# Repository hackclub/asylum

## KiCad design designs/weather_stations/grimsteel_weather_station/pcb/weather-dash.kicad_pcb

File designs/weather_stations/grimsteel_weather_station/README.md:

# grimsteel's weather station

## Features:
- Displays:
    - Weekly weather
    - Data from Home Assistant (soon)
- DHT11 sensor
- Two buttons
- Battery powering + charging
- Buzzer

## PCB
Here's a picture of my schematif! 

Schematic            |  PCB
:-------------------------:|:-------------------------:
  |  

*I'm using a WeMos ESP32-S2 module because of the added pins!*

[x] I ran DRC in KiCad and have made sure there are 0 errors!

## CAD Model:

The PCB is fastened using 3 M3 Heatset inserts and 3 M3 screws.
The case itself snaps together.

## Firmware overview

The firmware is written using ESP-IDF. It gets all data from Home Assistant

[x] I remembered to exclude any personal information, including API Keys, WiFi passwords, etc

## BOM
All prices must be in USD.

**Provided by dari // alex**:
- 1x WeMos S2 Mini WITHOUT FEMALE HEADERS
- 1x ST7735 1.8" LCD display WITHOUT FEMALE HEADERS. Male headers soldered!

**I will be sourcing the following parts with my grant**:
- 1x PCB from JLCPCB
    - $2 for 5x + $1.50 shipping
- 2x JST PH-2.0 connector + wires/plug [Aliexpress](https://www.aliexpress.us/item/3256806041370367.html) $1.08 (includes 5)
- 1x 3 pin SPDT switch - 0.5A [Aliexpress](https://www.aliexpress.us/item/2255800513009332.html) $0.84 (includes 10)
- 1x 1N5817 diode [Aliexpress](https://www.aliexpress.us/item/3256801365779334.html) $1.01 (includes 50)
- 1x TP4056 board [Aliexpress](https://www.aliexpress.us/item/3256804241424963.html) $1.29 (includes 5)
- 2x Tactile button cap - gray [Aliexpress](https://www.aliexpress.us/item/2251832842559353.html) $2.89 (includes 20)
- 3x M3/4.5mm, 3.5mm long Heatset Inserts  [Aliexpress](https://www.aliexpress.us/item/3256803396040989.html) $1.86 (includes 50)
- M3 heatset insert soldering iron tip [Aliexpress](https://www.aliexpress.us/item/3256806515637370.html) $2.37
- 1x 3pin Battery Spring compression contact (BC-35-3P) [Aliexpress](https://www.aliexpress.us/item/2255800016944760.html) $2.28 (includes 5)

**Total before tax**: $13.62 (all items are eligible for free shipping)

**I'll also be source the following parts myself since I already have them and would like to help Hack Club**:
- 1x 3D printed case
- 1x DHT11 board
- 2x 12mm push button
- 1x 10 ohm resistor
- 1x 1x3 female header (DHT11)
- 2x 2x8 male header (WeMos)
- 1x buzzer
- 1x Li-ion battery

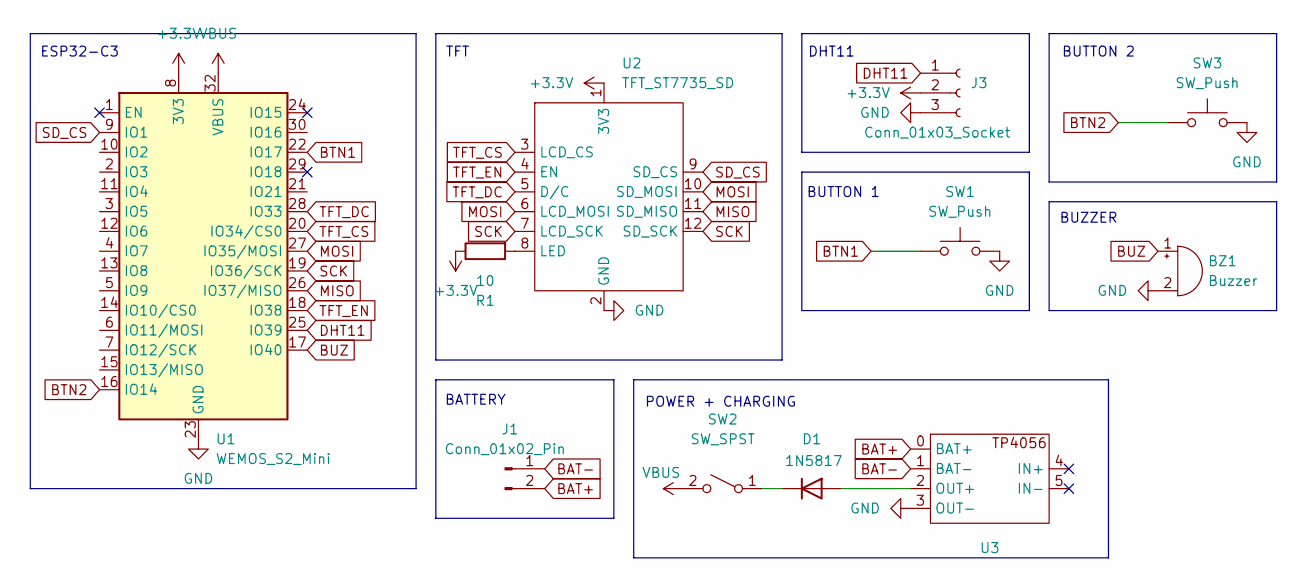
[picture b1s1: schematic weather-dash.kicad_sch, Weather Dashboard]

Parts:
BZ1: Buzzer; Buzzer_12x9.5RM7.6
D1: 1N5817; D_DO-41_SOD81_P7.62mm_Horizontal
J1: Conn_01x02_Pin; JST_PH_B2B-PH-K_1x02_P2.00mm_Vertical
J3: Conn_01x03_Socket; DHT11
R1: 10; R_Axial_DIN0207_L6.3mm_D2.5mm_P7.62mm_Horizontal
SW1, SW3: SW_Push; SW_PUSH_6mm_H4.3mm
SW2: SW_SPST; JST_PH_B2B-PH-K_1x02_P2.00mm_Vertical
U1: WEMOS_S2_Mini
U2: TFT_ST7735_SD
U3: TP4056

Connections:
+3.3V: J3.2, R1.1, U1.8 (3V3), U2.1 (3V3)
BAT+: J1.2, U3.0 (BAT+)
BAT-: J1.1, U3.1 (BAT-)
BTN1: SW1.1, U1.22 (IO17)
BTN2: SW3.1, U1.16 (IO14)
BUZ: BZ1.1 (+), U1.17 (IO40)
DHT11: J3.1, U1.25 (IO39)
GND: BZ1.2 (-), J3.3, SW1.2, SW3.2, U1.23 (GND), U2.2 (GND), U3.3 (OUT-)
MISO: U1.26 (IO37/MISO), U2.11 (SD_MISO)
MOSI: U1.27 (IO35/MOSI), U2.6 (LCD_MOSI), U2.10 (SD_MOSI)
unnamed: D1.2 (A), U3.2 (OUT+)
unnamed: D1.1 (K), SW2.1 (A)
unnamed: R1.2, U2.8 (LED)
SCK: U1.19 (IO36/SCK), U2.7 (LCD_SCK), U2.12 (SD_SCK)
SD_CS: U1.9 (IO1), U2.9 (SD_CS)
TFT_CS: U1.20 (IO34/CS0), U2.3 (LCD_CS)
TFT_DC: U1.28 (IO33), U2.5 (D/C)
TFT_EN: U1.18 (IO38), U2.4 (EN)
VBUS: SW2.2 (B), U1.32 (VBUS)

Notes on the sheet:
BUTTON 2
BUTTON 1
ESP32-C3
POWER + CHARGING
TFT
DHT11
BUZZER
BATTERY

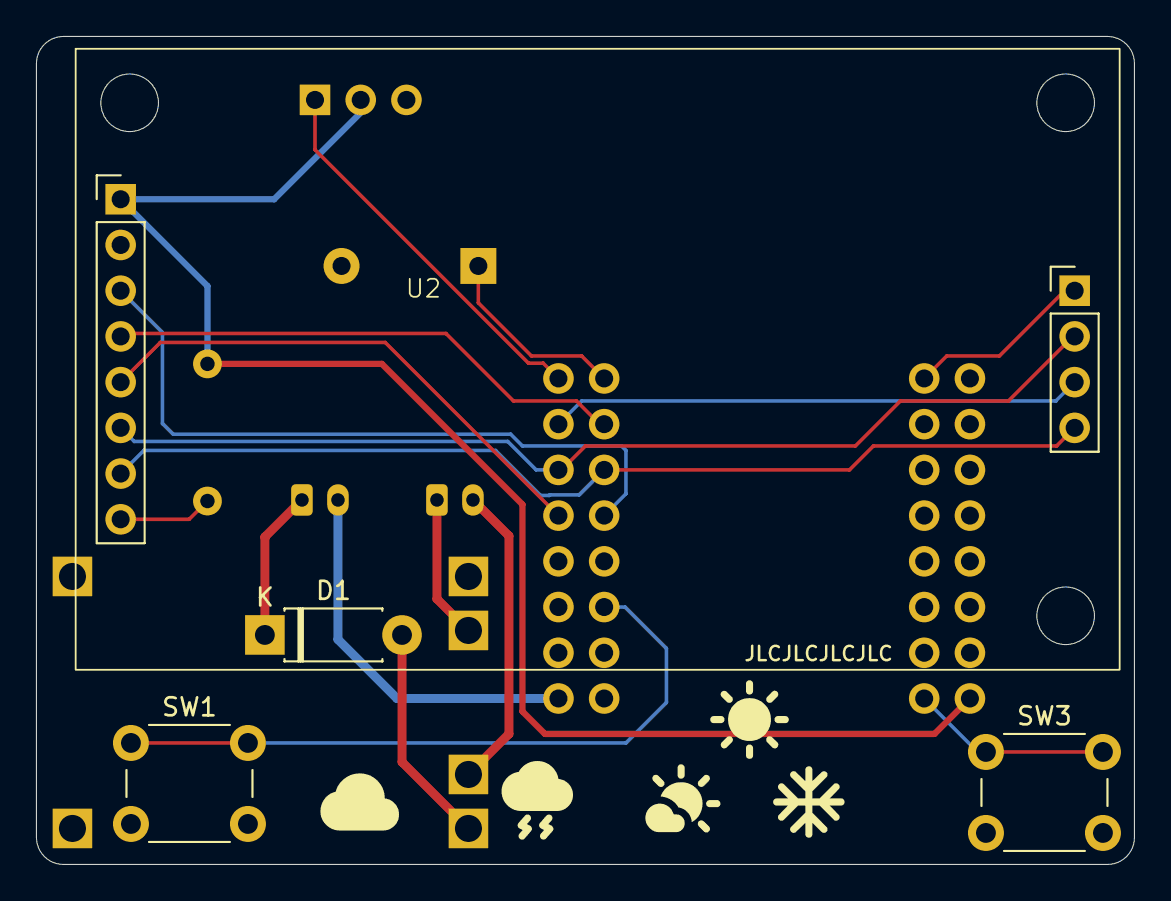
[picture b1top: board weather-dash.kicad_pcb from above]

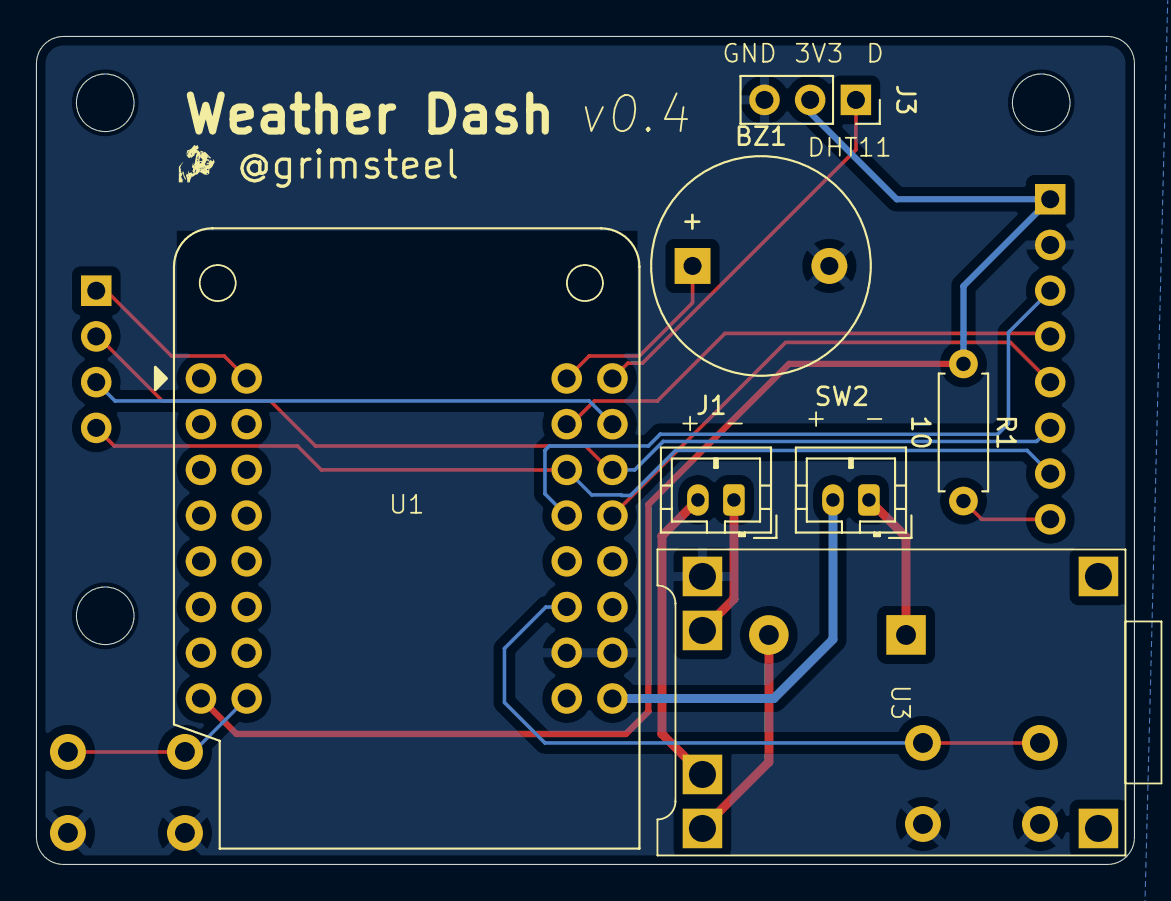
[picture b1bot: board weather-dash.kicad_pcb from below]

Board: 11 copper layers, 61.0 x 46.0 mm, 11 parts (7 on the bottom side), 19 nets.

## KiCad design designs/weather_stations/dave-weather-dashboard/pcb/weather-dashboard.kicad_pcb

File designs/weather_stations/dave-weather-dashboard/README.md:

# Dave's Weather Dashboard

This is a weather dashboard I made.

## Features

- Fetching from BMKG's API
- Displays: Weather information

## Firmware Overview

The firmware is located in the [firmware folder](./firmware) made using [PlatformIO](https://platformio.org/). To open using PlatformIO, open the [firmware](./firmware).

## CAD Model

The design was made using [Autodesk Fusion](https://www.autodesk.com/education/edu-software/fusion) is located in the [cad folder](./cad).

## PCB

The PCB was made using [KiCad](https://www.kicad.org/) 8.99 located in the [pcb folder](./pcb).

Schematic | PCB
:-:|:-:
 | 

## BOM

All prices must be in USD.

**Provided by dari // alex**:
- 1x WeMos S2 Mini WITHOUT FEMALE HEADERS
- 1x ST7735 1.8" LCD display WITHOUT FEMALE HEADERS. Male headers soldered!

**I will be sourcing the following parts with my grant**:

- 1x PCB from JLCPCB
    - $4 for 5x + $1.50 for shipping
- 2x 10 uF 1206 3216(mm) SMD Capacitor [Tokopedia](https://www.tokopedia.com/cosmic-iot/capacitor-10uf-10-uf-0603-kapasitor-microfarad-smd) $0.13
- 1x 18650 Li-ion Battery [Tokopedia](https://www.tokopedia.com/alladinshop/original-baterai-lion-18650-high-drain-real-capacity-2500mah-3-7v-3-7volt-li-ion) $0.76
- 1x Resistor SMD 1206 3216(mm) 50k Ohm [Tokopedia](https://www.tokopedia.com/smgjayatronik/resistor-smd-1206-50-kiloohm-50k-50-k) $0.13 (includes 10)
- 1x Resistor SMD 1206 3216 (mm) 10 Ohm [Tokopedia](https://www.tokopedia.com/smgjayatronik/resistor-smd-1206-10-ohm) $0.08 (includes 10)
- 1x Resistor SMD 1206 3216 (mm) 1k Ohm [Tokopedia](https://www.tokopedia.com/smgjayatronik/resistor-smd-1206-1-6k-1k6-ohm) $0.08 (includes 10)
- 1x Resistor SMD 1206 3216 (mm) 100k Ohm [Tokopedia](https://www.tokopedia.com/smgjayatronik/resistor-smd-1206-100-kiloohm-100k-100-k) $0.08 (includes 10)
- 1x O3401A SOT-23 MOSFET [Tokopedia](https://www.tokopedia.com/lisuinstrument/ao3401-3401-a19t-30v-p-channel-mosfet-ao3401a-sot-23-generic-biasa-3b2c) $0.02
- 1x LED SMD 1206 [Tokopedia](https://www.tokopedia.com/jogjarobotika/led-smd-1206-hijau) $0.02
- 1x 18650 Battery Holder [Tokopedia](https://www.tokopedia.com/mikro-automasi/dudukan-baterai-batre-18650-battery-holder-1-satu-slot) $0.13

Tokopedia before shipping: $1.37
Tokopedia after shipping: $4.14 (estimation)
Total: $8.64 (estimation)

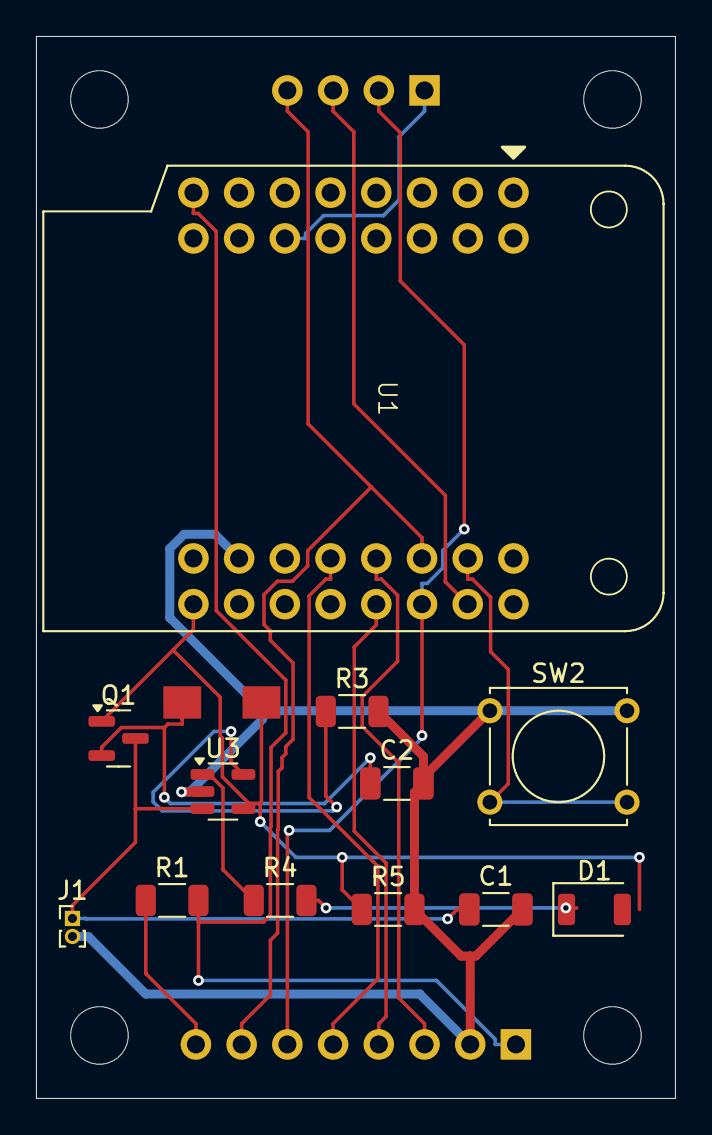
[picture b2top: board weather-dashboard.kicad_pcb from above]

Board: 2 copper layers, 35.5 x 59.0 mm, 14 parts (1 on the bottom side), 17 nets.

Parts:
C1: C1; C_1206_3216Metric
C2: C2; C_1206_3216Metric
D1: ORANGE; LED_1206_3216Metric_ReverseMount_Hole1.8x2.4mm
D2: D_Schottky; DO-214AC
J1: Conn_01x02_MountingPin; PinHeader_1x02_P1.00mm_Vertical
Q1: SL2301S; SOT-23
R1: R1; R_1206_3216Metric
R3: 50k; R_1206_3216Metric
R4: 1k; R_1206_3216Metric
R5: 100k; R_1206_3216Metric
SW2: SW_Omron_B3FS; SW_Tactile_Straight_KSA0Axx1LFTR
U1: WEMOS_S2_Mini
U3: MCP73831-2-OT; SOT-23-5
U4: U4; TFT_ST7735_SD

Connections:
+3V3: R1.2, U1.8 (3V3), U4.1 (3V3)
+BATT: C1.1, J1.1, Q1.3 (D), U3.3 (V_{BAT})
Button: SW2.2, U1.18 (IO38)
GND: C1.2, C2.2, J1.2, R3.2, R5.2, SW2.1, U1.23 (GND), U3.2 (V_{SS}), U4.2 (GND)
MISO: U1.26 (IO37/MISO), U4.11 (SD_MISO)
MOSI: U1.27 (IO35/MOSI), U4.6 (LCD_MOSI), U4.10 (SD_MOSI)
unnamed: D1.1 (K), R4.2
unnamed: R3.1, U3.5 (PROG)
unnamed: R4.1, U3.1 (STAT)
unnamed: R1.1, U4.8 (LED)
SCK: U1.19 (IO36/SCK), U4.7 (LCD_SCK), U4.12 (SD_SCK)
SD_CS: U1.14 (IO10/CS0), U4.9 (SD_CS)
TFT_CS: U1.20 (IO34/CS0), U4.3 (LCD_CS)
TFT_DC: U1.21 (IO21), U4.5 (D/C)
TFT_EN: U1.28 (IO33), U4.4 (EN)
VBUS: D1.2 (A), D2.2 (A), Q1.1 (G), R5.1, U1.32 (VBUS), U3.4 (V_{DD})
VCC: C2.1, D2.1 (K), Q1.2 (S)

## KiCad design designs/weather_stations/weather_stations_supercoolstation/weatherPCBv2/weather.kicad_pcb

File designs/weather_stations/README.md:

# weather station
Here's my submission for my weather station! Under the asylum "dragons_weather"

## Features:
- Displays:
    - Date
    - Temperature 
    - Settings
- 4 WS2812Bs for dynamic LED effects
- A switch for turning on and off
- Slider for settings

## PCB
Here's a picture of my schematic, I wired a Wemos ESP32-S3 module to a TFT display, 5 WS2812B LEDs, a slider for settings

Schematic            |  PCB
:-------------------------:|:-------------------------:

tic.png)  |  

[ x ] I ran DRC in KiCad and have made sure there are 0 errors!

## CAD Model:
Everything fits together using 4 M3 Heatset inserts

## Firmware overview
Firmware is written in aurdino, it grabs data from a API. Code for turining it off and on, slider and basic settings are written

[ x ] I remembered to exclude any personal information, including API Keys, WiFi passwords, etc

#BOM
**Provided by dari // alex**:
- 1x WeMos S2 Mini WITHOUT FEMALE HEADERS
- 1x ST7735 1.8" LCD display WITHOUT FEMALE HEADERS. Male headers soldered!

I will buy 4 WS2812Bs, which will cost me $0.8 in total.
I will be sourcing the following parts with my grant:
- 1x PCB from JLCPCB
    - $2 for 5x + $1.50 shipping

- 1x SPDT slide switch [(ADAFRUIT)](https://www.adafruit.com/product/4219) $2.95

Total before tax: $6.5

I'll also be source the following parts myself since I already have them and would like to help Hack Club:

- 3d PRINT

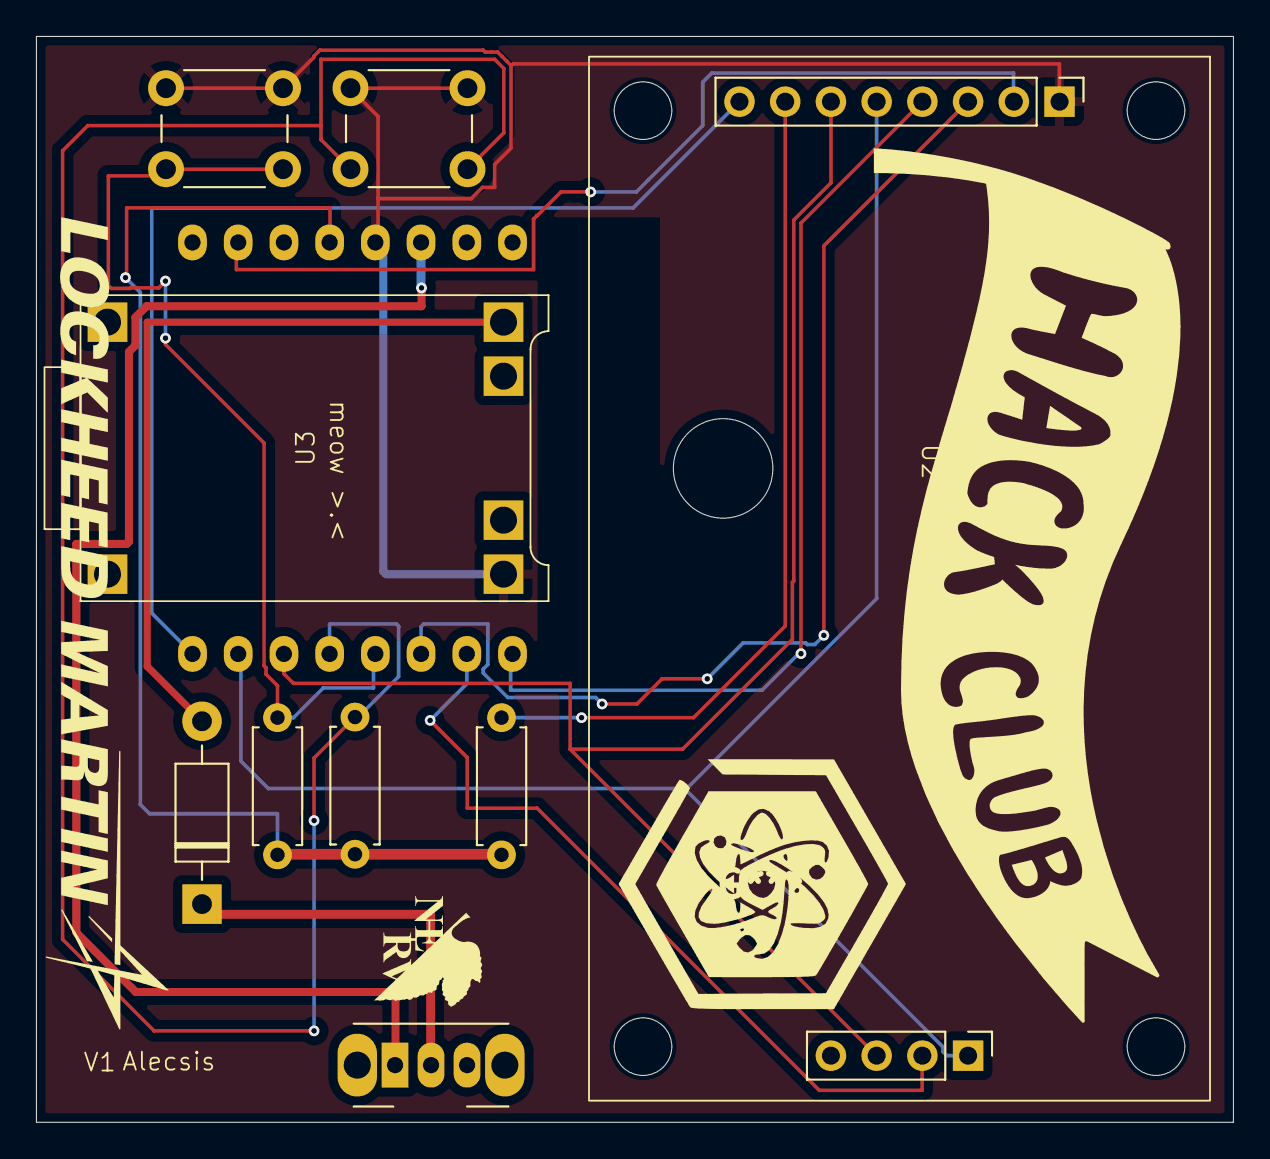
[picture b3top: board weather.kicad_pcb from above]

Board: 2 copper layers, 66.5 x 60.3 mm, 10 parts (1 on the bottom side), 15 nets.

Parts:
D1: 1N5817; D_DO-41_SOD81_P10.16mm_Horizontal
R2: 10; R_Axial_DIN0207_L6.3mm_D2.5mm_P7.62mm_Horizontal
R5, R6: 10K; R_Axial_DIN0207_L6.3mm_D2.5mm_P7.62mm_Horizontal
SW1, SW2: SW_Push; SW_PUSH_6mm_H9.5mm
SW3: SW_SPDT; SW_Slide_SPDT_Angled_CK_OS102011MA1Q
U1: WEMOS_C3_mini
U2: TFT_ST7735_SD
U3: TP4056

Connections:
+3.3V: R2.2, R5.1, R6.1, U1.12 (3.3V)
AO: U1.1 (A1), U2.4 (AO)
B1: R5.2, SW1.1, U1.4 (A4)
B2: R6.2, SW2.1, U1.5 (A5)
Batt_Out: D1.2 (A), U3.2 (OUT+)
CS: U1.10, U2.2 (~CS)
GND: SW1.2, SW2.2, U1.13 (GND), U2.1 (GND), U3.3 (OUT-)
MISO: U1.2 (A2), U2.10 (SD_MISO)
MOSI: U1.7 (7/RGB_LED), U2.5 (SDA), U2.9 (SD_MOSI)
unnamed: D1.1 (K), SW3.2 (B)
unnamed: R2.1, U2.7 (LED)
RESET: U1.3 (A3), U2.3 (RESET)
SCK: U1.6, U2.6 (SCK), U2.11 (SD_SCK)
SD_CS: U1.8, U2.8 (SD_CS)
VCC: SW3.1 (A), U1.14 (VBUS)

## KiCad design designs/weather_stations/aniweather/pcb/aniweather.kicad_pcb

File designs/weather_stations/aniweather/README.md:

<h1 align="center">Aniweather - Your personal anime weather station!</h1>

This is a 3D weather station! You can choose between displaying daily waifu pics and the current weather. **No external libraries used!**

Made for #asylum. The main API code is at https://github.com/cheyao/short with nest :D

To change the settings, edit `firmware/settings.h`! The weather info is mostly parsed on nest.

[ x ] I ran DRC in KiCad and have made sure there are 0 errors!

### BOM 
Provided by dari // alex:
- 1x WeMos S2 Mini (as a cheaper replacement for the S2) WITHOUT FEMALE HEADERS
- 1x ST7735 1.8" LCD display WITHOUT FEMALE HEADERS. Male headers soldered!

Purchasing from HQ:
- 2x 1N4148 at ???$

I will be sourcing the following parts with my grant:
- 1x PCB from JLCPCB
    - $2 for 5x + $1.50 shipping
- 2x 2-1825910-7             0,17 $ - 0,51 $
- 1x NR3015T2R2M             0,31 $ - 0,31 $ 
- 4x FG16X7R1E106KRT06       0,84 $ - 3,36 $
- 1x TPS63001DRCR            2,16 $ - 2,16 $
- 1x 3D printed case         self print

Total: 8.34 $ + Lipo from aliexpress

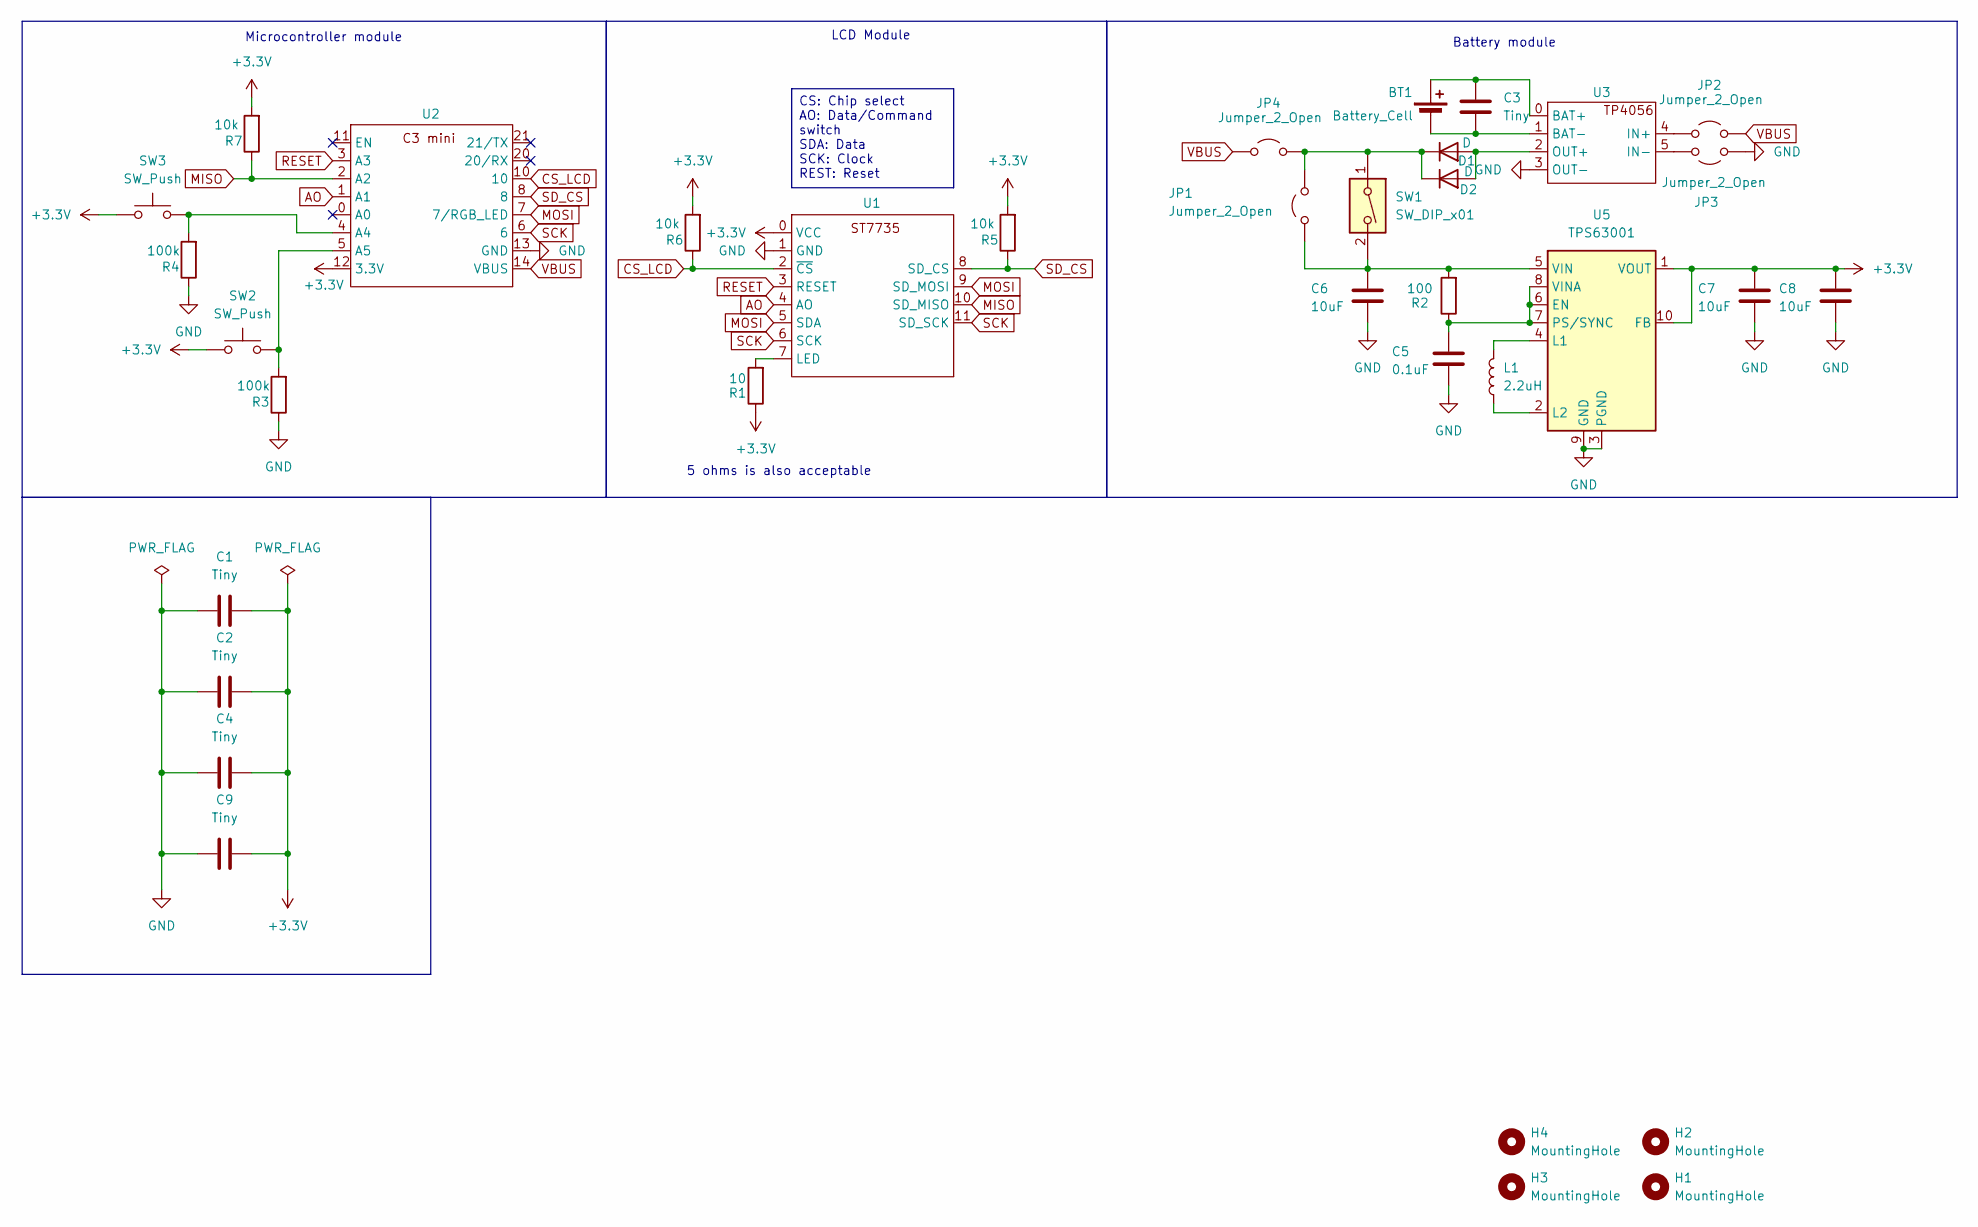
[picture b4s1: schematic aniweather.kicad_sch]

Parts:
BT1: Battery_Cell; TestPoint_2Pads_Pitch5.08mm_Drill1.3mm
C1, C2, C3, C4, C9: Tiny; C_Disc_D5.0mm_W2.5mm_P2.50mm
C5: 0.1uF; C_Disc_D5.0mm_W2.5mm_P2.50mm
C6, C7, C8: 10uF; C_Disc_D5.0mm_W2.5mm_P2.50mm
D1, D2: D; D_DO-35_SOD27_P7.62mm_Horizontal
H1, H2, H3, H4: MountingHole; MountingHole_3.2mm_M3
JP1, JP2, JP3, JP4: Jumper_2_Open; SolderJumper-2_P1.3mm_Open_Pad1.0x1.5mm
L1: 2.2uH; NR3015T2R2M
R1: 10; R_Axial_DIN0207_L6.3mm_D2.5mm_P10.16mm_Horizontal
R2: 100; R_Axial_DIN0207_L6.3mm_D2.5mm_P10.16mm_Horizontal
R3, R4: 100k; R_Axial_DIN0207_L6.3mm_D2.5mm_P10.16mm_Horizontal
R5, R6, R7: 10k; R_Axial_DIN0207_L6.3mm_D2.5mm_P10.16mm_Horizontal
SW1: SW_DIP_x01; SW_DIP_SPSTx01_Slide_9.78x4.72mm_W7.62mm_P2.54mm
SW2, SW3: SW_Push; SW_PUSH_6mm
U1: ST7735
U2: WEMOS_C1_mini
U3: TP4056
U5: TPS63001; Texas_DRC0010J_ThermalVias

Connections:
+3.3V: C1.2, C2.2, C4.1, C7.1, C8.1, C9.1, R1.1, R5.2, R6.2, R7.2, SW2.1, SW3.1, U1.0 (VCC), U2.12 (3.3V), U5.1 (VOUT), U5.10 (FB)
AO: U1.4 (AO), U2.1 (A1)
CS_LCD: R6.1, U1.2 (~CS), U2.10
GND: C1.1, C2.1, C4.2, C5.2, C6.2, C7.2, C8.2, C9.2, JP3.1 (A), R3.1, R4.1, U1.1 (GND), U2.13 (GND), U3.3 (OUT-), U5.3 (PGND), U5.9 (GND), U5.11 (PGND)
MISO: R7.1, U1.10 (SD_MISO), U2.2 (A2)
MOSI: U1.5 (SDA), U1.9 (SD_MOSI), U2.7 (7/RGB_LED)
unnamed: BT1.1 (+), C3.1, U3.0 (BAT+)
unnamed: BT1.2 (-), C3.2, U3.1 (BAT-)
unnamed: D1.2 (A), D2.2 (A), U3.2 (OUT+)
unnamed: D1.1 (K), D2.1 (K), JP1.2 (B), JP4.2 (B), SW1.1
unnamed: C6.1, JP1.1 (A), R2.2, SW1.2, U5.5 (VIN)
unnamed: JP2.1 (A), U3.4 (IN+)
unnamed: JP3.2 (B), U3.5 (IN-)
unnamed: R1.2, U1.7 (LED)
unnamed: R4.2, SW3.2, U2.4 (A4)
unnamed: R3.2, SW2.2, U2.5 (A5)
unnamed: C5.1, R2.1, U5.6 (EN), U5.7 (PS/SYNC), U5.8 (VINA)
unnamed: L1.2, U5.4 (L1)
unnamed: L1.1, U5.2 (L2)
RESET: U1.3 (RESET), U2.3 (A3)
SCK: U1.6 (SCK), U1.11 (SD_SCK), U2.6
SD_CS: R5.1, U1.8 (SD_CS), U2.8
VBUS: JP2.2 (B), JP4.1 (A), U2.14 (VBUS)

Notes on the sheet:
Microcontroller module
Battery module
5 ohms is also acceptable
LCD Module
CS: Chip select AO: Data/Command switch SDA: Data SCK: Clock REST: Reset

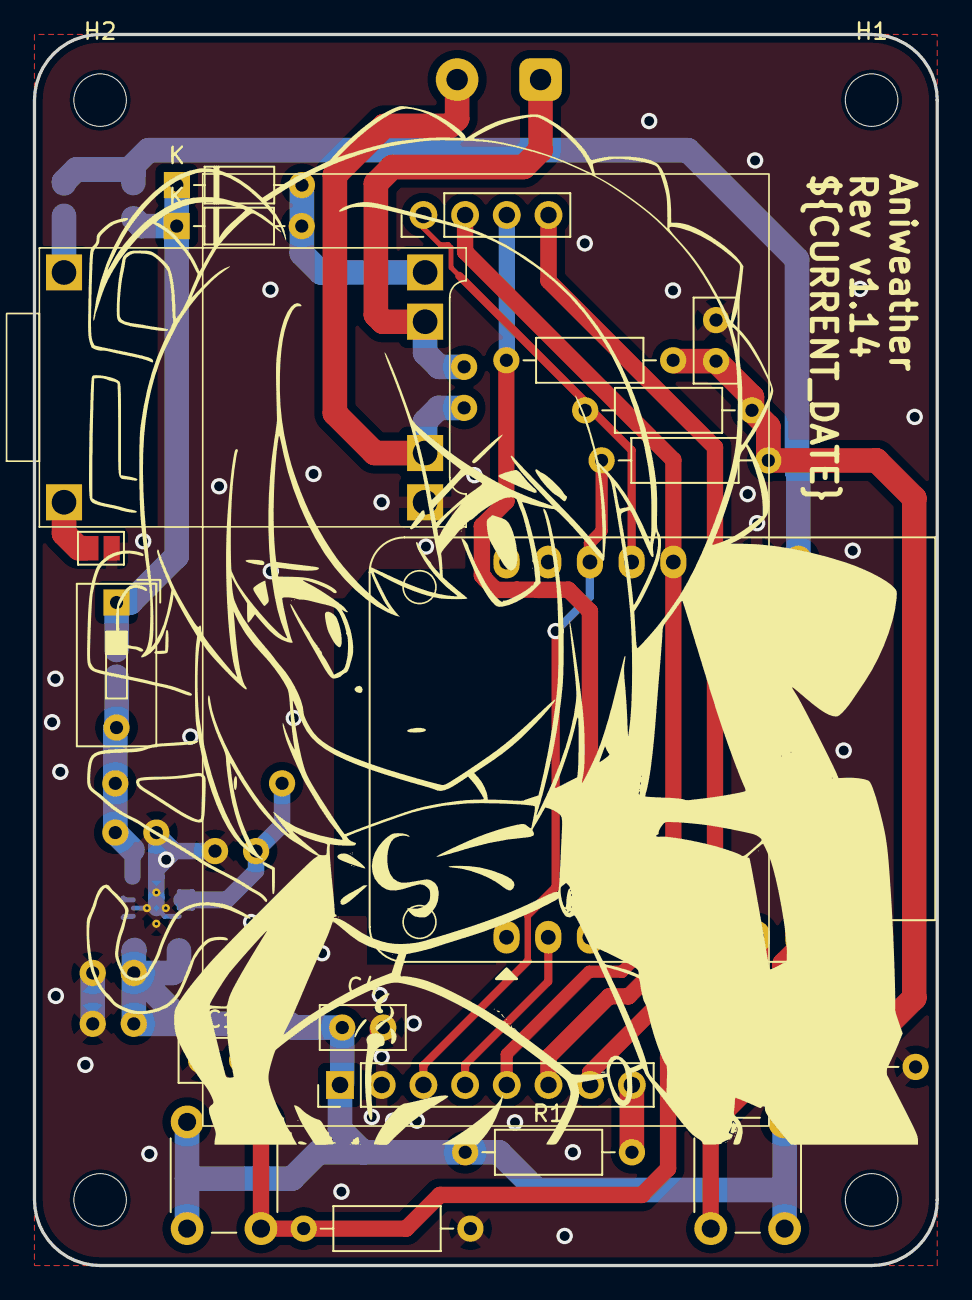
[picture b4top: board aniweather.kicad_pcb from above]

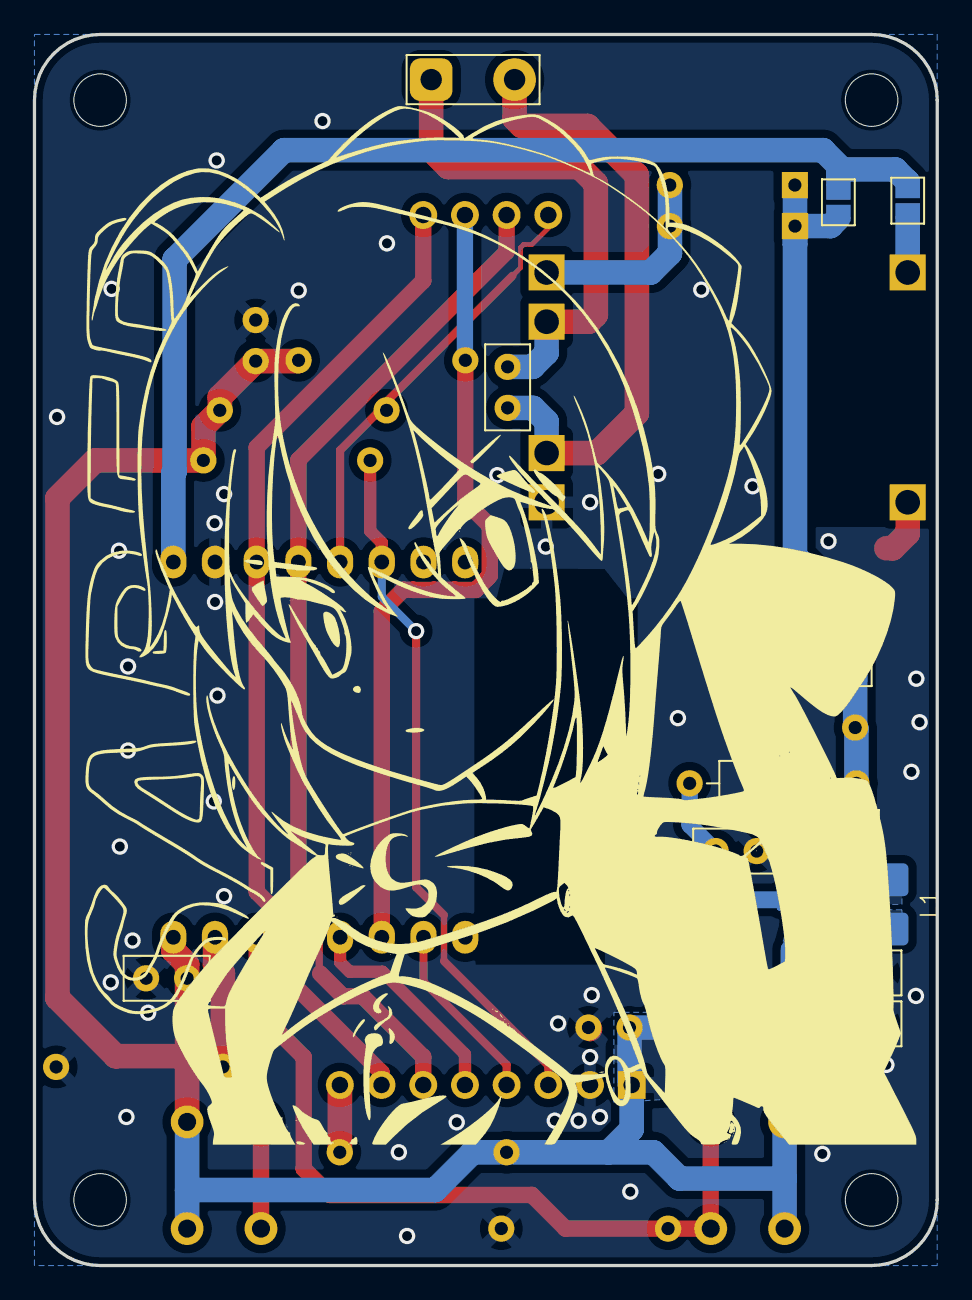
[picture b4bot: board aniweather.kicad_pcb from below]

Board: 2 copper layers, 55.0 x 75.0 mm, 37 parts (14 on the bottom side), 23 nets.

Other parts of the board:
G1, G2: LOGO

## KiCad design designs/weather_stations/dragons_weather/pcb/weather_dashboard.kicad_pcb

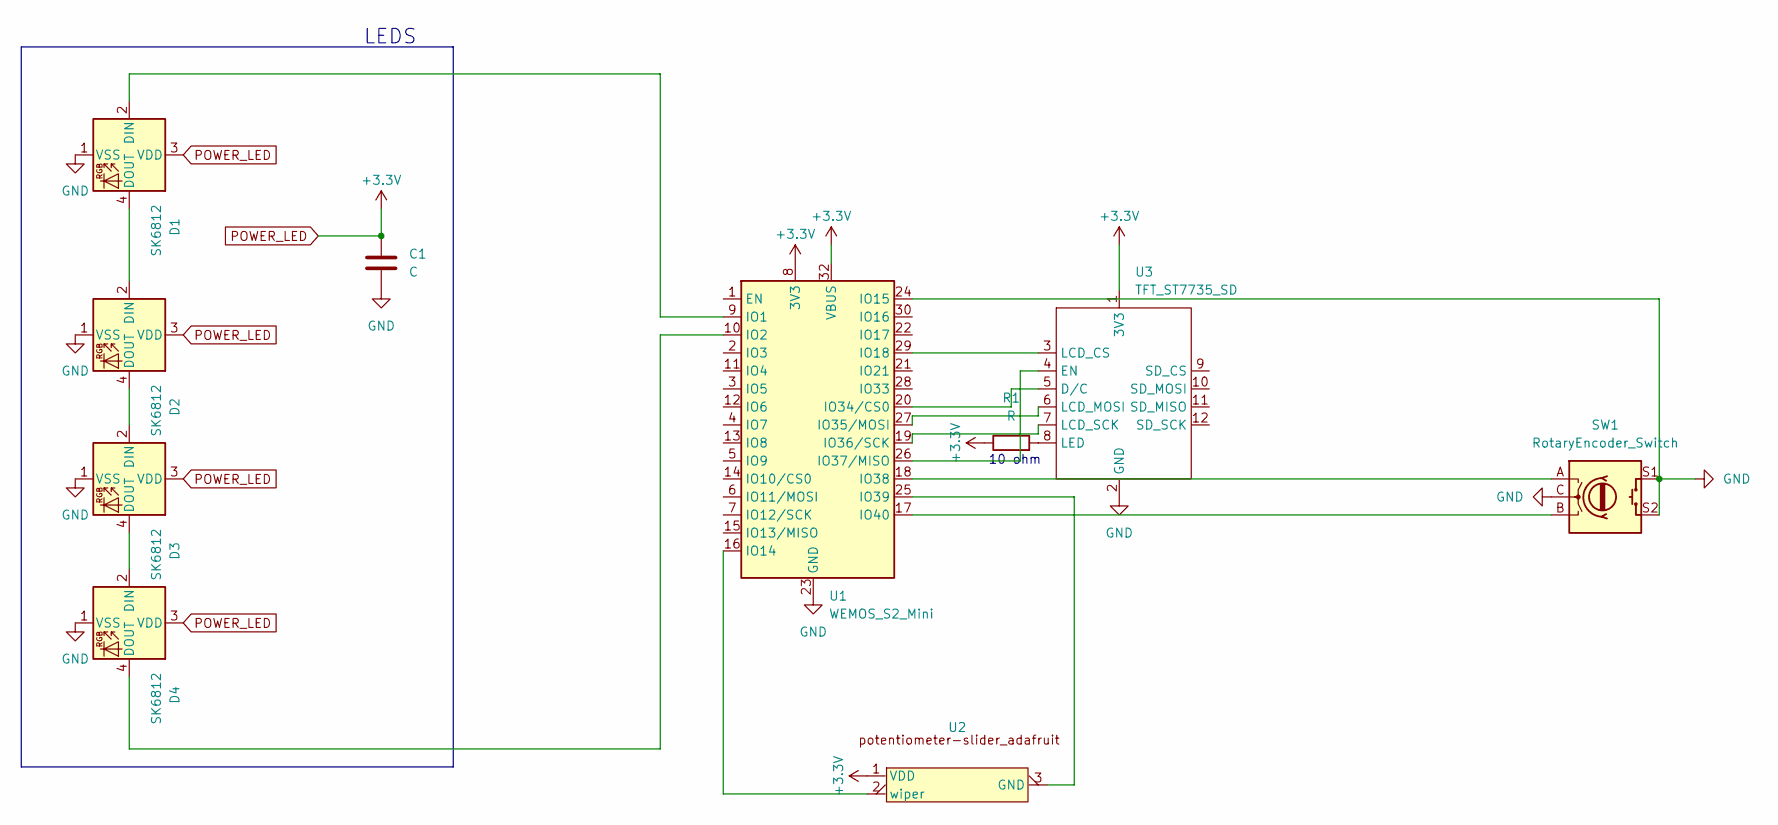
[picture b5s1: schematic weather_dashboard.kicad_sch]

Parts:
C1: C; CP_Axial_L10.0mm_D4.5mm_P15.00mm_Horizontal
D1, D2, D3, D4: SK6812; LED_SK6812_PLCC4_5.0x5.0mm_P3.2mm
R1: R; R_Array_SIP4
SW1: RotaryEncoder_Switch; RotaryEncoder_Alps_EC11E-Switch_Vertical_H20mm
U1: WEMOS_S2_Mini
U2: Potienometer-slider_adafruit
U3: TFT_ST7735_SD

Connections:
GND: C1.2, D1.1 (VSS), D2.1 (VSS), D3.1 (VSS), D4.1 (VSS), SW1.C, SW1.S1, SW1.S2, U1.23 (GND), U1.24 (IO15), U3.2 (GND)
unnamed: D1.2 (DIN), U1.9 (IO1)
unnamed: D1.4 (DOUT), D2.2 (DIN)
unnamed: D2.4 (DOUT), D3.2 (DIN)
unnamed: D3.4 (DOUT), D4.2 (DIN)
unnamed: D4.4 (DOUT), U1.10 (IO2)
unnamed: U1.16 (IO14), U2.2 (wiper)
unnamed: U1.29 (IO18), U3.3 (LCD_CS)
unnamed: U1.20 (IO34/CS0), U3.5 (D/C)
unnamed: U1.27 (IO35/MOSI), U3.6 (LCD_MOSI)
unnamed: U1.19 (IO36/SCK), U3.7 (LCD_SCK)
unnamed: U1.26 (IO37/MISO), U3.4 (EN)
unnamed: SW1.A, U1.18 (IO38)
unnamed: U1.25 (IO39), U2.3 (GND)
unnamed: SW1.B, U1.17 (IO40)
unnamed: R1.2, U3.8 (LED)
POWER_LED: C1.1, D1.3 (VDD), D2.3 (VDD), D3.3 (VDD), D4.3 (VDD), R1.1, U1.8 (3V3), U1.32 (VBUS), U2.1 (VDD), U3.1 (3V3)

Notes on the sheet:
LEDS
10 ohm

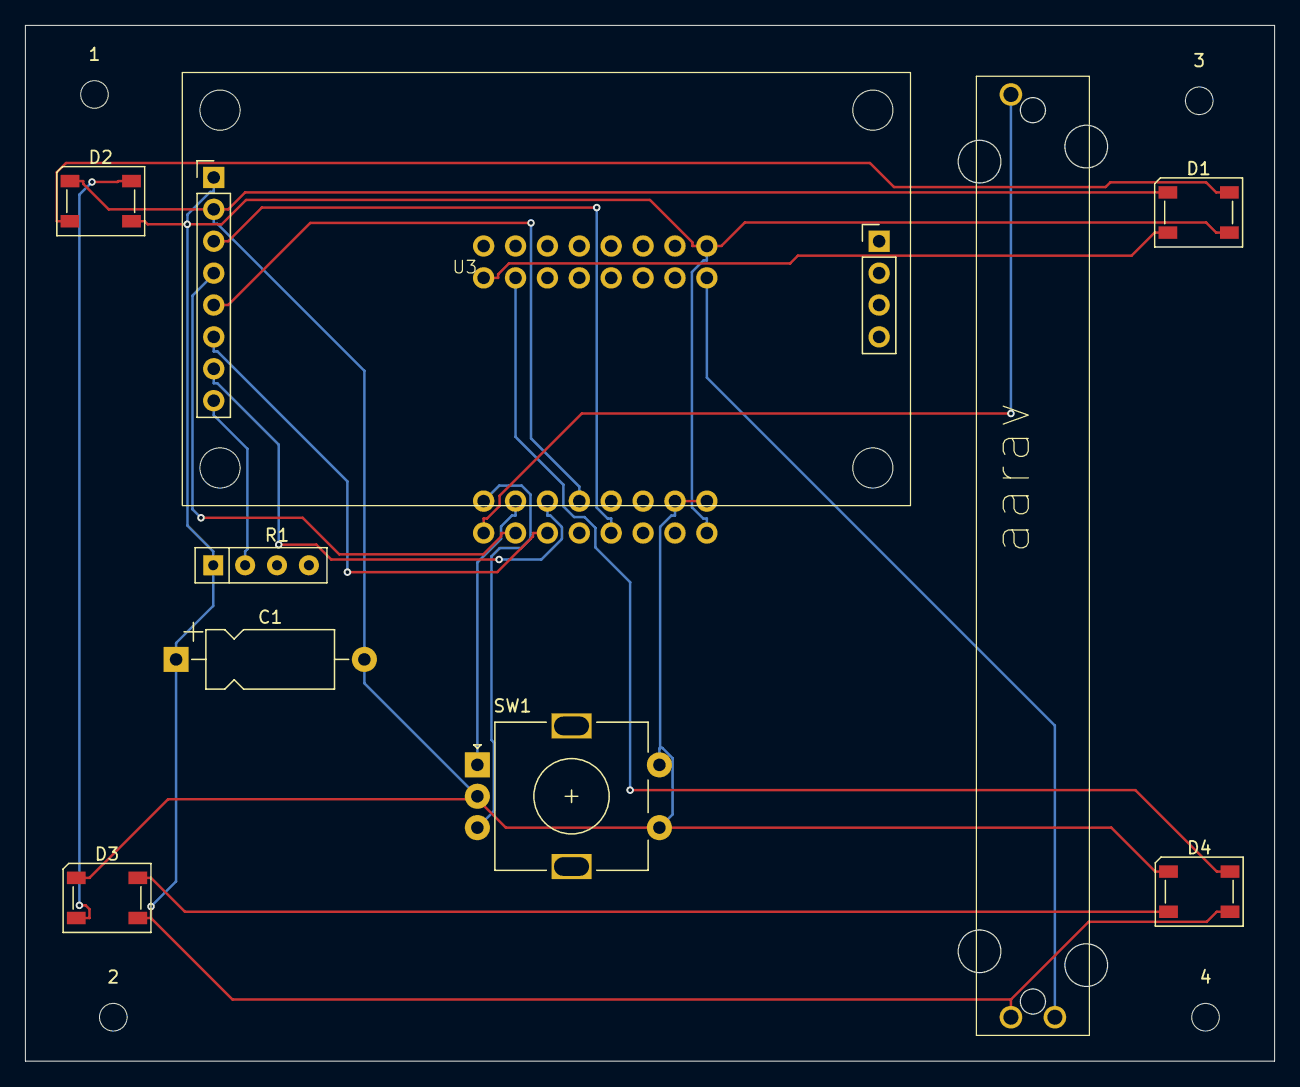
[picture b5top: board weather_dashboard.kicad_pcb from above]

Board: 2 copper layers, 99.5 x 82.5 mm, 14 parts (1 on the bottom side), 17 nets.

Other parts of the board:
1, 2, 3, 4: MountingHole_2.2mm_M2

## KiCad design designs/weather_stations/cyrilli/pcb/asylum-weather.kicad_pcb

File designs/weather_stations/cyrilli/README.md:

# cyrilli's weather station submission

<div align="center">
    
    &nbsp;
    &nbsp;
    
</div>

## BOM

- 1x Wemos/Lolin ESP32-C3 board
- 1x 1.8 inch TFT display
- 2x ELM3052 Triac
    - C142300
- 1x 75 Ohm 0603 Resistor
    - C4275
- 1x 10 Ohm 1206 Resistor
    - C17903
- 3x 2x8P 2.54mm Female Header
    - C5160823
- 8x M3 25mm Double-ended Standoff
- 2x M3 16mm Double-ended Standoff
- 4x M3 50mm Screw
- 2x M3 16mm Screw

## Planned Use

I plan to use this as a small display for agenda items or connect it to my computer to use as a status panel. I will also run wires to our garage door to act as a smart door opener.

## Design Process

The design was inspired by 龙少's stacked homebrew CPU design. Since the minimum order for PCBs is 5, I used the extra boards to sandwich the main board, acting as a case without needing extra 3D printed components. The PCB is perfectly square so that two layers can be rotated and stacked for the bottome case, covering all the drill holes and cutouts of each other. Pin connections between the LCD and the ESP32 was chosen to permit visually pleasing routing on a single layer.

## Case

I am planning to stack some unpopulated PCBs vertically for a homebrew-cpu-like "case" instead of using 3D printed parts.

## Firmware

Written in CircuitPython, will be expanded once I have hardware to test on.

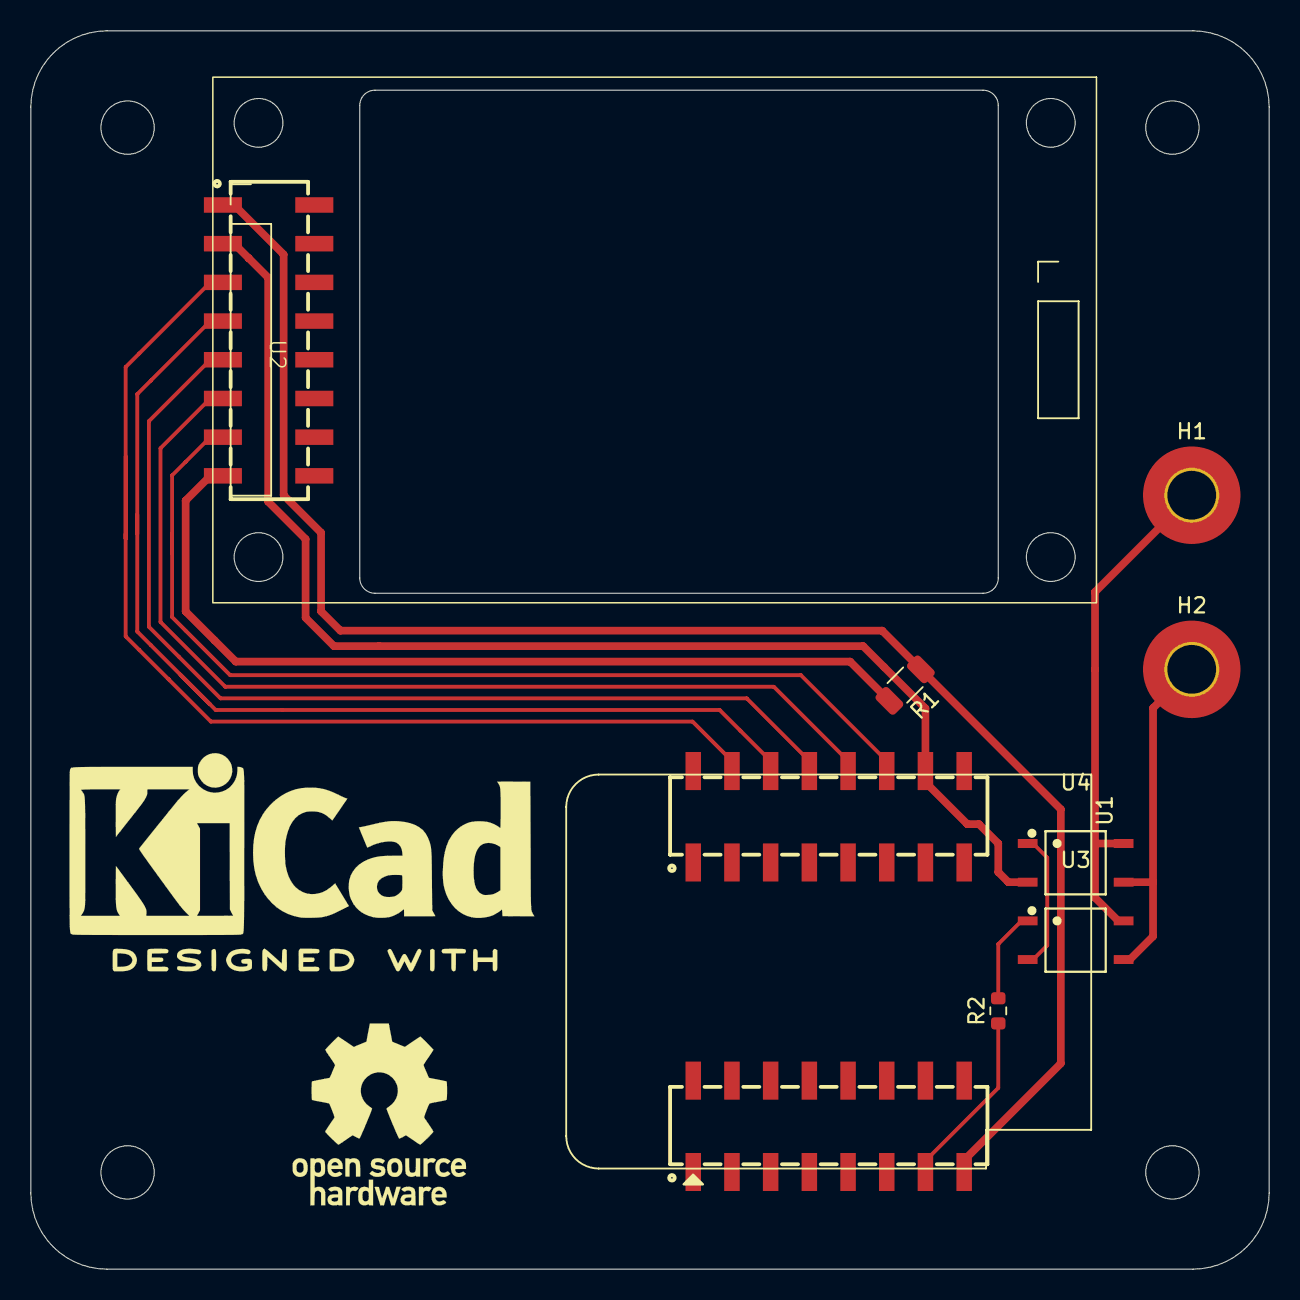
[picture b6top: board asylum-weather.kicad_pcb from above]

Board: 2 copper layers, 81.3 x 81.3 mm, 10 parts (0 on the bottom side), 13 nets.

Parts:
H1, H2: MountingHole_Pad; MountingHole_3.2mm_M3_Pad_TopBottom
J1, J2: Conn_02x08_Counter_Clockwise; HDR-SMD_16P-P2.54-V-F-R2-C8-LS7.1
R1: 10; R_1206_3216Metric
R2: 75; R_0603_1608Metric
U1: WEMOS_C3_Mini; WEMOS_C3_1
U2: TFT_ST7735_SD
U3, U4: ELM3052(TA); SOP-4_L4.4-W4.0-P2.54-LS7.0-TL

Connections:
unnamed: H1.1, U3.4 (Terminal), U4.4 (Terminal)
unnamed: H2.1, U3.3 (Terminal), U4.3 (Terminal)
unnamed: R1.2, U2.8 (LED)
unnamed: R2.2, U3.1 (Anode)
unnamed: U3.2 (Cathode), U4.1 (Anode)
P7: J1.7, R2.1
P8: J1.8, R1.1, U2.1 (3V3)
P10: J2.10, U2.2 (GND), U4.2 (Cathode)
P11: J2.11, U2.7 (LCD_SCK)
P12: J2.12, U2.6 (LCD_MOSI)
P13: J2.13, U2.5 (D/C)
P14: J2.14, U2.4 (EN)
P15: J2.15, U2.3 (LCD_CS)
